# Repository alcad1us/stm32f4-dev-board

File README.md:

# STM32F4 Development Board – First PCB Design

This repository contains my first STM32-based PCB design.

The board is designed as a simple development board around an STM32F4 series microcontroller.
It includes:
- Power supply and regulation
- USB interface
- SWD programming and debugging interface
- Basic clock and decoupling circuitry

## Project Scope

This project was mainly focused on learning the **hardware design workflow**:
- Drawing the schematic
- Power and bypass (decoupling) capacitor placement
- USB D+/D− differential pair routing
- Pull-up resistor usage
- Debug interface connections
- PCB placement and routing

Rather than aiming for a production-ready board, the goal was to understand *why* certain hardware design rules exist and how they affect a real PCB.

## Visual Overview

Below are some visuals from the design process to give a quick overview without opening the design files.

### PCB Layout

### 3D View

## Folder Structure

- pcb/ → KiCad PCB layout files
- schematic/ → KiCad schematic files
- images/ → Schematic, PCB and 3D render images

## Notes

- This is my **first PCB design**, so the focus was learning and experimentation.
- Many design decisions were made by researching, testing, and iterating.
- The project helped me clearly see the difference between theory and real-world PCB layout constraints.

## Tools Used

- KiCad
- STM32 reference documentation

## Status

Design completed.  
The project is kept as a learning reference and portfolio example.

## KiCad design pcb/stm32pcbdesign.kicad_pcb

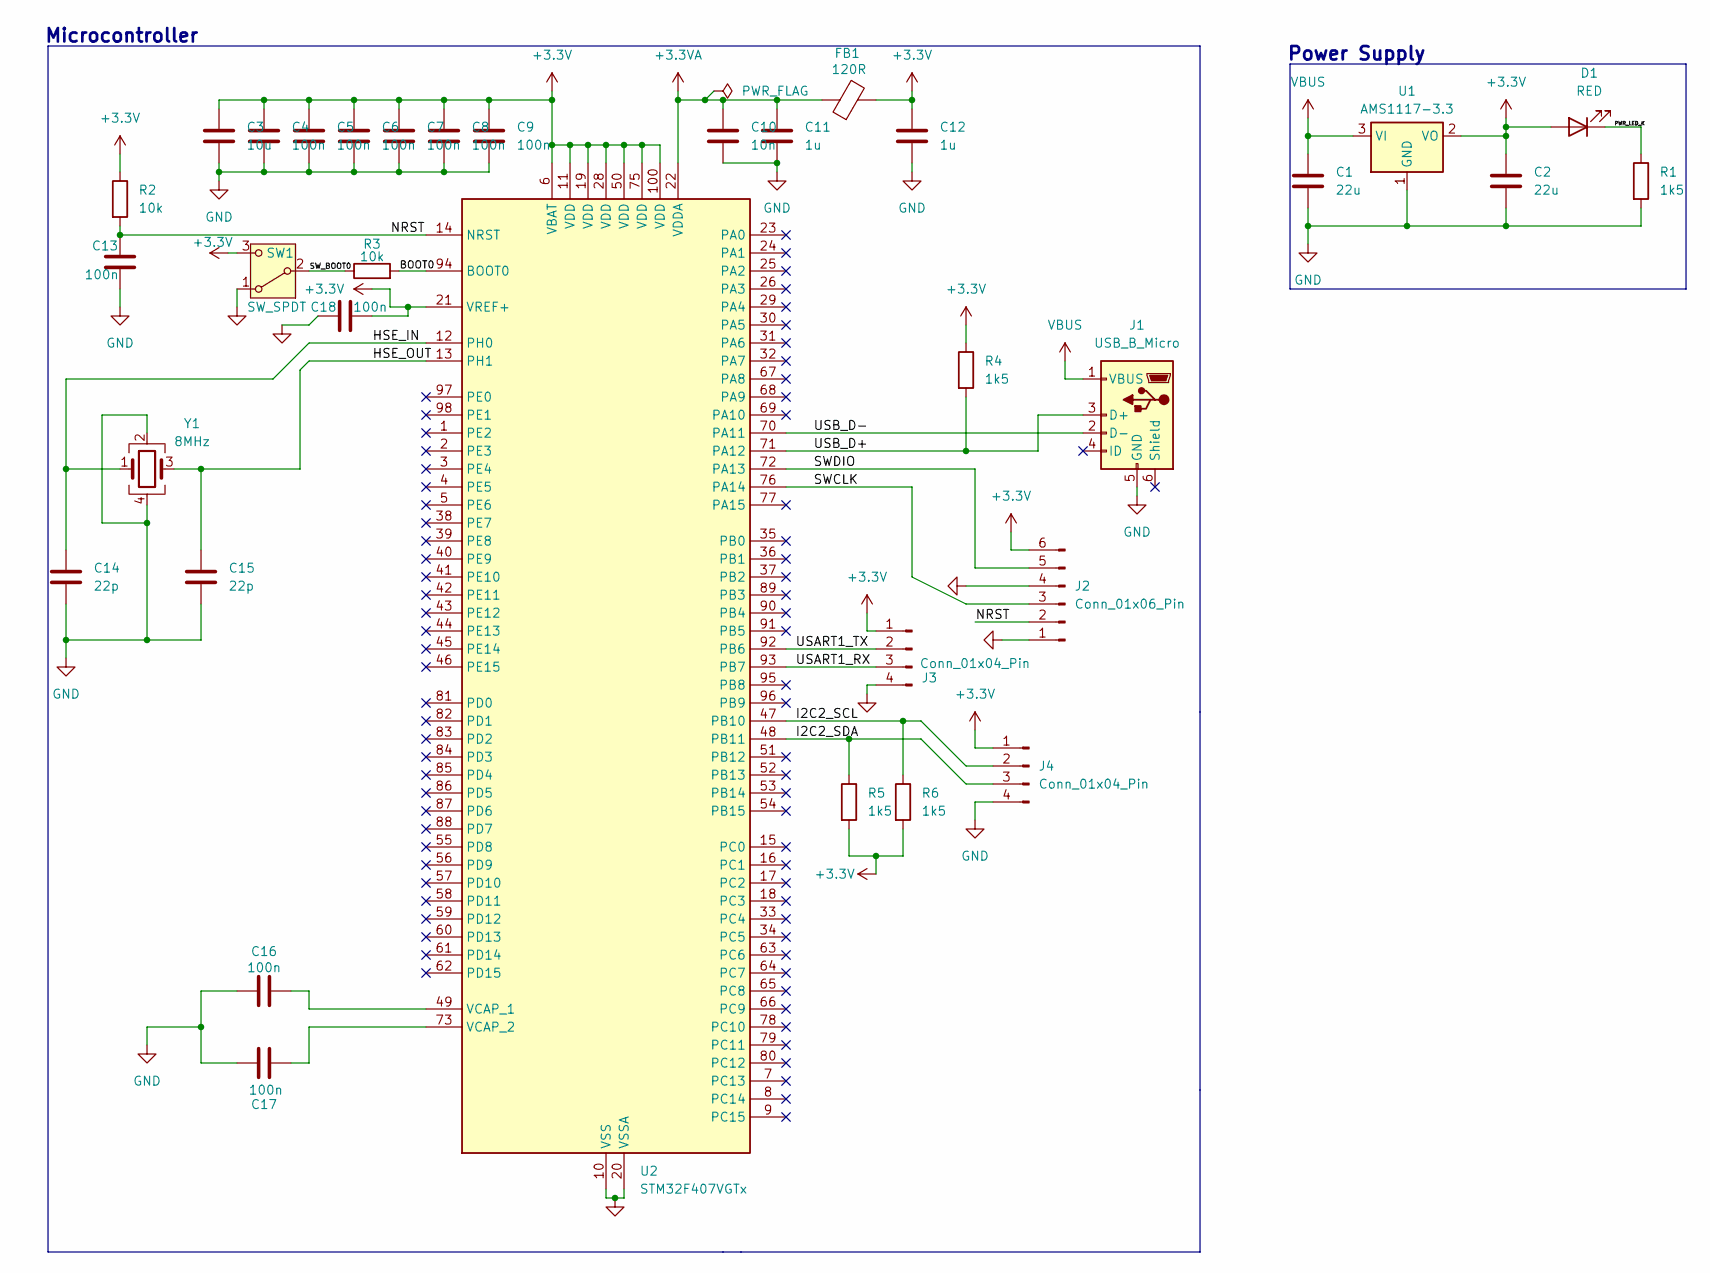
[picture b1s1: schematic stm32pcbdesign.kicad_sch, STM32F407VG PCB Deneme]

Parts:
C1, C2: 22u; C_0805_2012Metric
C3: 10u; C_0603_1608Metric
C4, C5, C6, C7, C8, C9, C13, C16, C17, C18: 100n; C_0402_1005Metric
C10: 10n; C_0402_1005Metric
C11, C12: 1u; C_0402_1005Metric
C14, C15: 22p; C_0402_1005Metric
D1: RED; LED_0603_1608Metric
FB1: 120R; L_0603_1608Metric
J1: USB_B_Micro; USB_Micro-B_Wuerth_629105150521
J2: Conn_01x06_Pin; PinHeader_1x06_P2.54mm_Vertical
J3, J4: Conn_01x04_Pin; PinHeader_1x04_P2.54mm_Vertical
R1, R4, R5, R6: 1k5; R_0402_1005Metric
R2, R3: 10k; R_0402_1005Metric
SW1: SW_SPDT; SW_SPDT_PCM12
U1: AMS1117-3.3; SOT-223-3_TabPin2
U2: STM32F407VGTx; LQFP-100_14x14mm_P0.5mm
Y1: 8MHz; Crystal_SMD_3225-4Pin_3.2x2.5mm

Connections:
+3.3V: C2.1, C3.1, C4.1, C5.1, C6.1, C7.1, C8.1, C9.1, C12.1, C18.2, D1.2 (A), FB1.2, J2.6, J3.1, J4.1, R2.1, R4.1, R5.2, R6.2, SW1.3 (C), U1.2 (VO), U2.6 (VBAT), U2.11 (VDD), U2.19 (VDD), U2.21 (VREF+), U2.28 (VDD), U2.50 (VDD), U2.75 (VDD), U2.100 (VDD)
+3.3VA: C10.1, C11.1, FB1.1, U2.22 (VDDA)
/BOOT0: R3.2, U2.94 (BOOT0)
/HSE_IN: C14.1, U2.12 (PH0), Y1.1
/HSE_OUT: C15.1, U2.13 (PH1), Y1.3
/I2C2_SCL: J4.2, R6.1, U2.47 (PB10)
/I2C2_SDA: J4.3, R5.1, U2.48 (PB11)
/NRST: C13.1, J2.2, R2.2, U2.14 (NRST)
/PWR_LED_K: D1.1 (K), R1.1
/SWCLK: J2.3, U2.76 (PA14)
/SWDIO: J2.5, U2.72 (PA13)
/SW_BOOT0: R3.1, SW1.2 (B)
/USART1_RX: J3.3, U2.93 (PB7)
/USART1_TX: J3.2, U2.92 (PB6)
/USB_D+: J1.3 (D+), R4.2, U2.71 (PA12)
/USB_D-: J1.2 (D-), U2.70 (PA11)
GND: C1.2, C2.2, C3.2, C4.2, C5.2, C6.2, C7.2, C8.2, C9.2, C10.2, C11.2, C12.2, C13.2, C14.2, C15.2, C16.1, C17.1, C18.1, J1.5 (GND), J2.1, J2.4, J3.4, J4.4, R1.2, SW1.1 (A), U1.1 (GND), U2.10 (VSS), U2.20 (VSSA), U2.27 (VSS), U2.74 (VSS), U2.99 (VSS), Y1.2, Y1.4
unnamed: C16.2, U2.49 (VCAP_1)
unnamed: C17.2, U2.73 (VCAP_2)
VBUS: C1.1, J1.1 (VBUS), U1.3 (VI)

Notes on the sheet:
Power Supply
Microcontroller

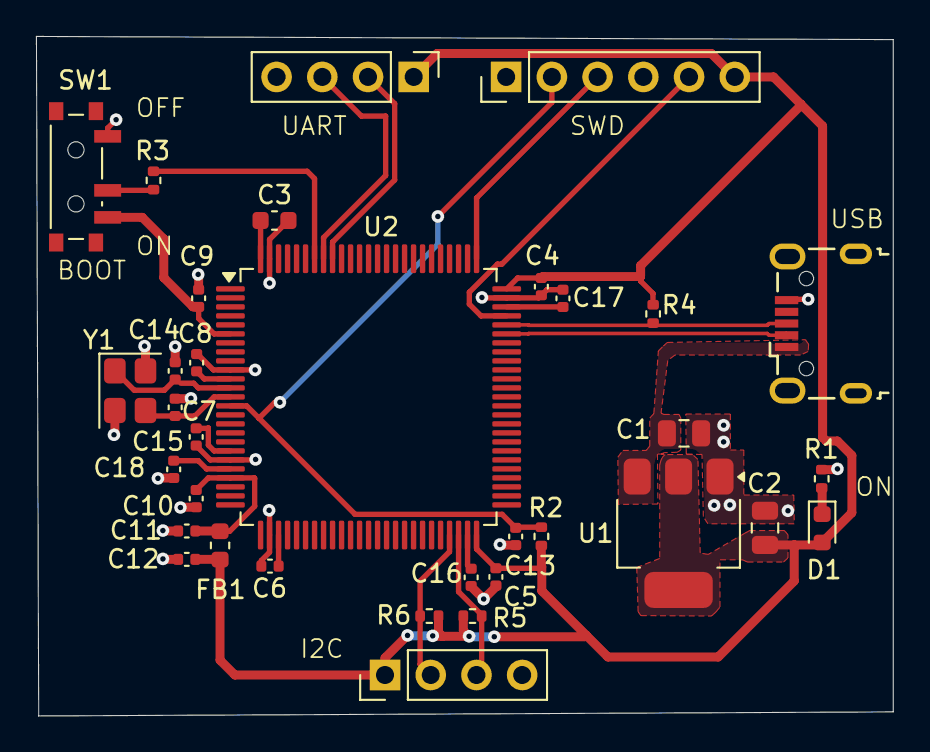
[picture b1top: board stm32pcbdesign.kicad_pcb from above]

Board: 2 copper layers, 47.6 x 37.8 mm, 34 parts (0 on the bottom side), 20 nets.

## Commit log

2026-02-06 Remove placeholder README
2026-02-06 Add schematic design files
2026-02-06 Add project README
